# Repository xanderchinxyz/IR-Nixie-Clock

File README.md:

# IR-Nixie-Clock
All of the code and PCB files for my RGBW Neopixel Matrix

Check out the YouTube video: https://youtu.be/nEOyhyJHx2M

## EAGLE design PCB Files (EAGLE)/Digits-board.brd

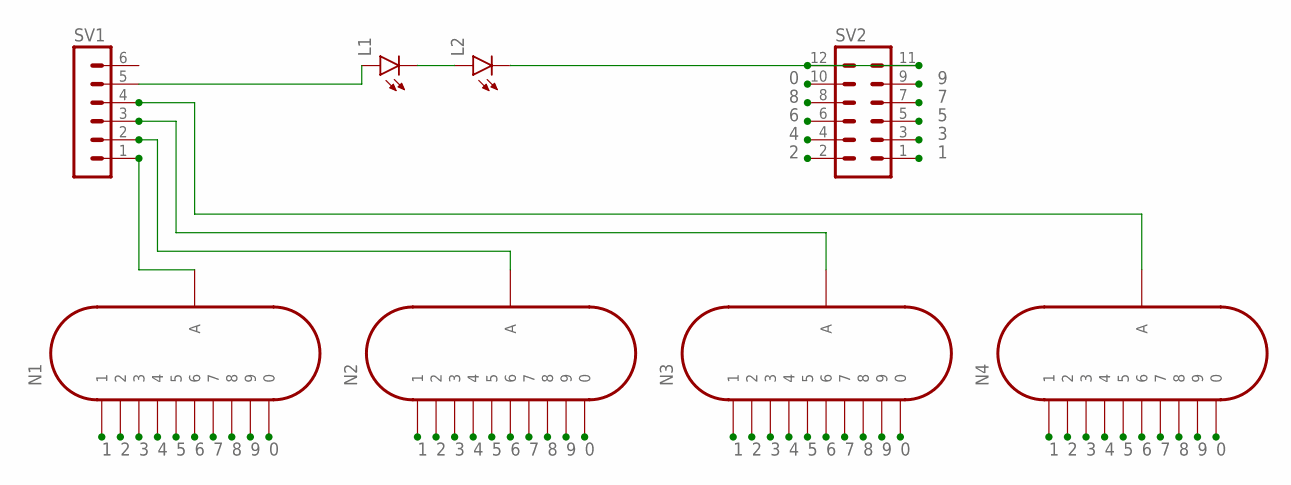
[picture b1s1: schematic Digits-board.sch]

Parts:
L1, L2: LED5MM
N1, N2, N3, N4: IN-12A; IN-12
SV1: MA06-1
SV2: MA06-2

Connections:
0: N1.0, N2.0, N3.0, N4.0, SV2.10
1: N1.1, N2.1, N3.1, N4.1, SV2.1
2: N1.2, N2.2, N3.2, N4.2, SV2.2
3: N1.3, N2.3, N3.3, N4.3, SV2.3
4: N1.4, N2.4, N3.4, N4.4, SV2.4
5: N1.5, N2.5, N3.5, N4.5, SV2.5
6: N1.6, N2.6, N3.6, N4.6, SV2.6
7: N1.7, N2.7, N3.7, N4.7, SV2.7
8: N1.8, N2.8, N3.8, N4.8, SV2.8
9: N1.9, N2.9, N3.9, N4.9, SV2.9
unnamed: L1.K (C), L2.A
unnamed: L1.A, SV1.5
unnamed: N4.A, SV1.4
unnamed: N3.A, SV1.3
unnamed: N2.A, SV1.2
unnamed: N1.A, SV1.1
unnamed: L2.K (C), SV2.11, SV2.12

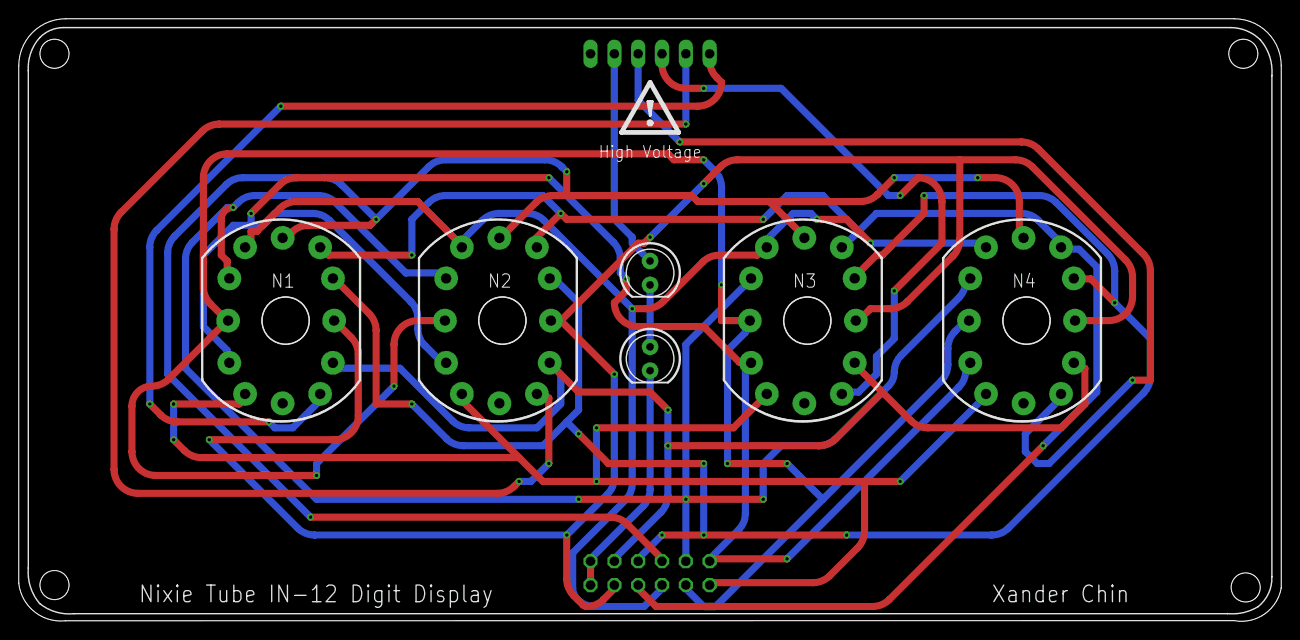
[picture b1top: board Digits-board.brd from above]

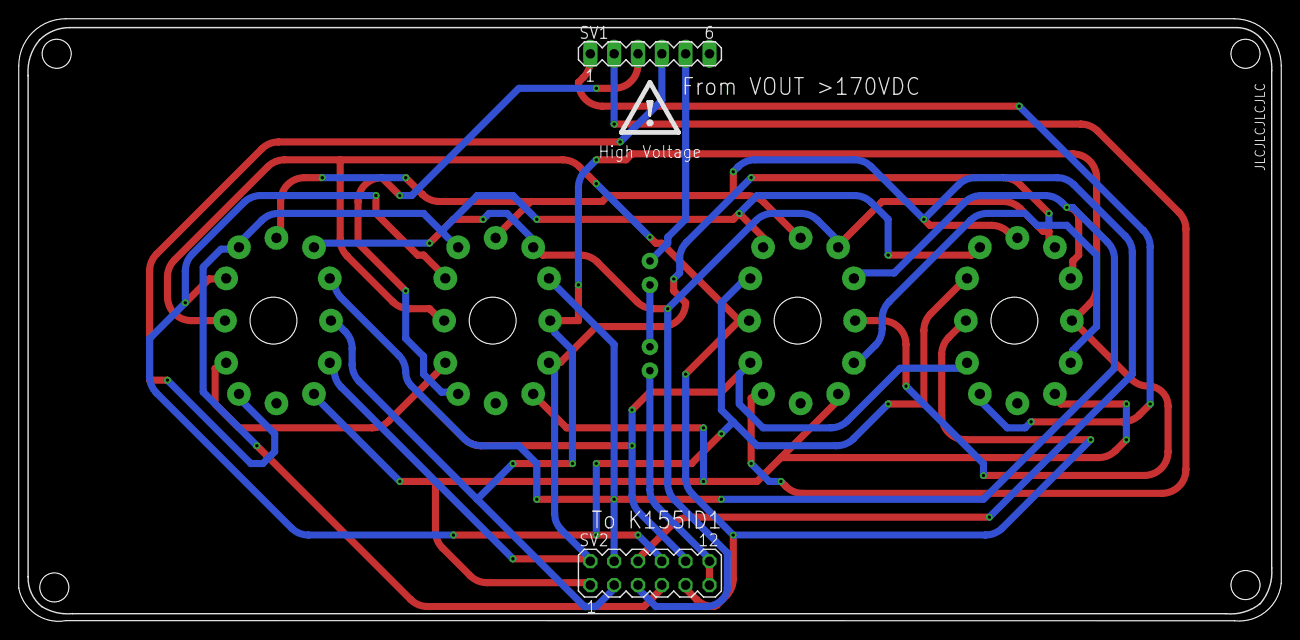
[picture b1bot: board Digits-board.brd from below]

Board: 2 copper layers, 134.6 x 64.2 mm, 10 parts (3 on the bottom side), 17 nets.

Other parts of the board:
U$1, U$2: CAUTION-HIGH-VOLTAGE

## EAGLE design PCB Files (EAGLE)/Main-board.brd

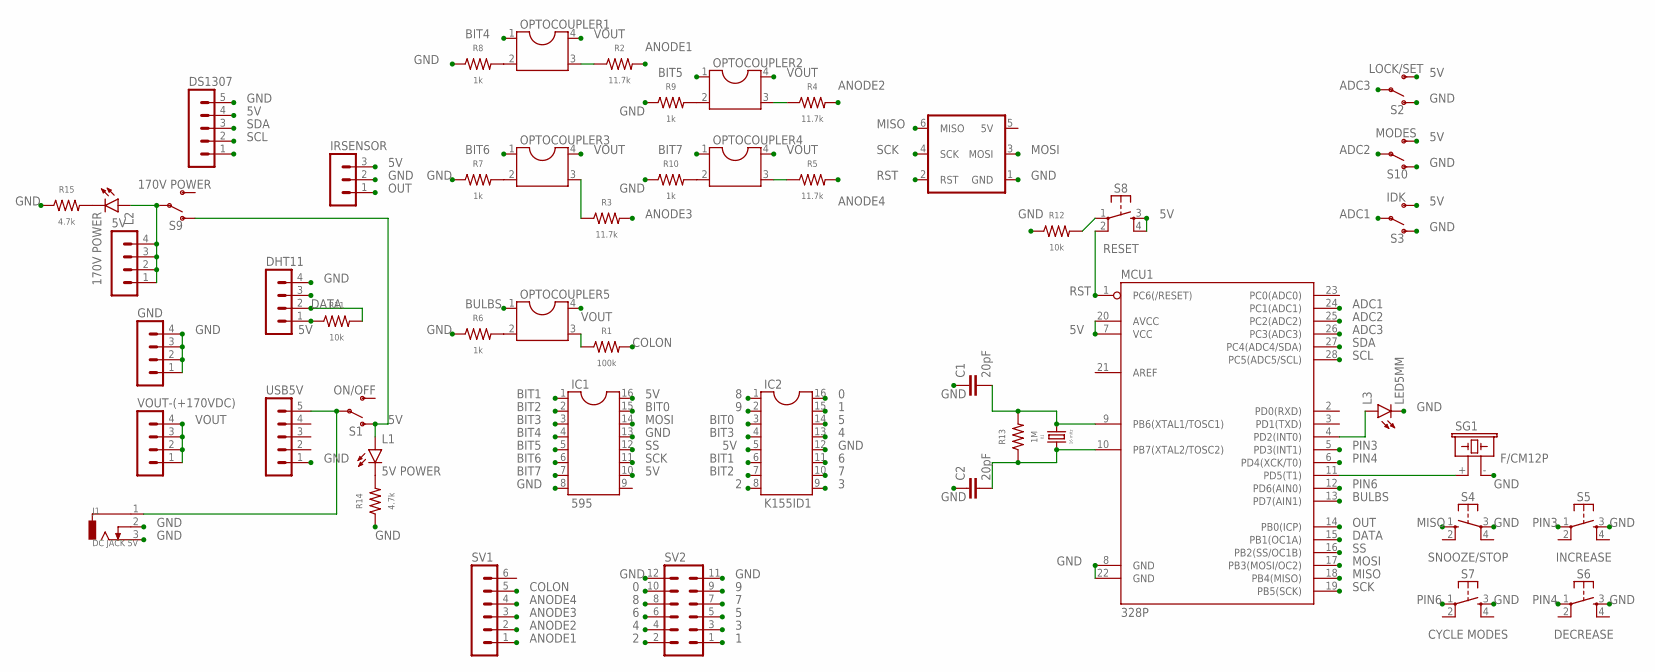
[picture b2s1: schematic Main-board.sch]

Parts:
5V: MA04-1
C1, C2: 20pF; CAP-PTH-2.54
DHT11: MA04-1
DS1307: MA05-1
GND: MA04-1
H1: ISP_HEADER; ICSP
IC1: 595; DIL16
IC2: K155ID1; DIL16
IRSENSOR: MA03-1
J1: DC JACK 5V; PJ-202AH
L1: 5V POWER; LED3MM
L2: 170V POWER; LED3MM
L3: LED5MM
MCU1: 328P; DIP28
OPTOCOUPLER1, OPTOCOUPLER2, OPTOCOUPLER3, OPTOCOUPLER4, OPTOCOUPLER5: DIL4; DIL04
R1: 100k; 0207/10
R2, R3, R4, R5: 11.7k; 0207/10
R6, R7, R8, R9, R10: 1k; 0207/10
R11, R12: 10k; 0207/10
R13: 1M; 0207/10
R14, R15: 4.7k; 0207/10
S1: ON/OFF; EG1218
S2: LOCK/SET; EG1218
S3: IDK; EG1218
S4: SNOOZE/STOP; B3F-40XX-ROUND
S5: INCREASE; TACTILE_SWITCH_PTH_6.0MM
S6: DECREASE; TACTILE_SWITCH_PTH_6.0MM
S7: CYCLE MODES; TACTILE_SWITCH_PTH_6.0MM
S8: RESET; TACTILE_SWITCH_PTH_6.0MM
S9: 170V POWER; EG1218
S10: MODES; EG1218
SG1: F/CM12P
SV1: MA06-1
SV2: MA06-2
USB5V: MA05-1
VOUT-(+170VDC): MA04-1
X1: 16 mHz; HC49US

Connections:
0: IC2.16, SV2.10
1: IC2.15, SV2.1
2: IC2.8, SV2.2
3: IC2.9, SV2.3
4: IC2.13, SV2.4
5: IC2.14, SV2.5
5V: DHT11.1, DS1307.4, H1.5 (5V), IC1.10, IC1.16, IC2.5, IRSENSOR.3, L1.A, MCU1.7 (VCC), MCU1.20 (AVCC), R11.1, S1.O, S2.S, S3.S, S8.3 (S), S8.4 (S1), S9.O, S10.S
6: IC2.11, SV2.6
7: IC2.10, SV2.7
8: IC2.1, SV2.8
9: IC2.2, SV2.9
ADC1: MCU1.24 (PC1(ADC1)), S3.P
ADC2: MCU1.25 (PC2(ADC2)), S10.P
ADC3: MCU1.26 (PC3(ADC3)), S2.P
ANODE1: R2.2, SV1.1
ANODE2: R4.2, SV1.2
ANODE3: R3.2, SV1.3
ANODE4: R5.2, SV1.4
BIT0: IC1.15, IC2.3
BIT1: IC1.1, IC2.6
BIT2: IC1.2, IC2.7
BIT3: IC1.3, IC2.4
BIT4: IC1.4, OPTOCOUPLER1.1
BIT5: IC1.5, OPTOCOUPLER2.1
BIT6: IC1.6, OPTOCOUPLER3.1
BIT7: IC1.7, OPTOCOUPLER4.1
BULBS: MCU1.13 (PD7(AIN1)), OPTOCOUPLER5.1
COLON: R1.2, SV1.5
DATA: DHT11.2, MCU1.15 (PB1(OC1A)), R11.2
GND: C1.1, C2.1, DHT11.4, DS1307.5, GND.1, GND.2, GND.3, GND.4, H1.1 (GND), IC1.8, IC1.13, IC2.12, IRSENSOR.2, J1.2, J1.3, L3.K (C), MCU1.8 (GND), MCU1.22 (GND), R6.1, R7.1, R8.1, R9.1, R10.1, R12.1, R14.1, R15.1, S2.O, S3.O, S4.3, S5.3 (S), S6.3 (S), S7.3 (S), S10.O, SG1.- (2), SV2.11, SV2.12, USB5V.1
MISO: H1.6 (MISO), MCU1.18 (PB4(MISO)), S4.1 (S)
MOSI: H1.3 (MOSI), IC1.14, MCU1.17 (PB3(MOSI/OC2))
unnamed: OPTOCOUPLER3.3, R3.1
unnamed: L1.K (C), R14.2
unnamed: OPTOCOUPLER1.3, R2.1
unnamed: OPTOCOUPLER2.3, R4.1
unnamed: OPTOCOUPLER5.2, R6.2
unnamed: OPTOCOUPLER3.2, R7.2
unnamed: OPTOCOUPLER1.2, R8.2
unnamed: OPTOCOUPLER2.2, R9.2
unnamed: OPTOCOUPLER4.2, R10.2
unnamed: OPTOCOUPLER4.3, R5.1
unnamed: L2.K (C), R15.2
unnamed: R12.2, S8.1
unnamed: OPTOCOUPLER5.3, R1.1
unnamed: C1.2, MCU1.9 (PB6(XTAL1/TOSC1)), R13.2, X1.2
unnamed: C2.2, MCU1.10 (PB7(XTAL2/TOSC2)), R13.1, X1.1
unnamed: 5V.1, 5V.2, 5V.3, 5V.4, L2.A, S9.P
unnamed: J1.1, S1.P, USB5V.5
unnamed: L3.A, MCU1.4 (PD2(INT0))
unnamed: MCU1.11 (PD5(T1)), SG1.+ (1)
OUT: IRSENSOR.1, MCU1.14 (PB0(ICP))
PIN3: MCU1.5 (PD3(INT1)), S5.1
PIN4: MCU1.6 (PD4(XCK/T0)), S6.1
PIN6: MCU1.12 (PD6(AIN0)), S7.1
RST: H1.2 (RST), MCU1.1 (PC6(/RESET)), S8.2 (P1)
SCK: H1.4 (SCK), IC1.11, MCU1.19 (PB5(SCK))
SCL: DS1307.2, MCU1.28 (PC5(ADC5/SCL))
SDA: DS1307.3, MCU1.27 (PC4(ADC4/SDA))
SS: IC1.12, MCU1.16 (PB2(SS/OC1B))
VOUT: OPTOCOUPLER1.4, OPTOCOUPLER2.4, OPTOCOUPLER3.4, OPTOCOUPLER4.4, OPTOCOUPLER5.4, VOUT-(+170VDC).1, VOUT-(+170VDC).2, VOUT-(+170VDC).3, VOUT-(+170VDC).4

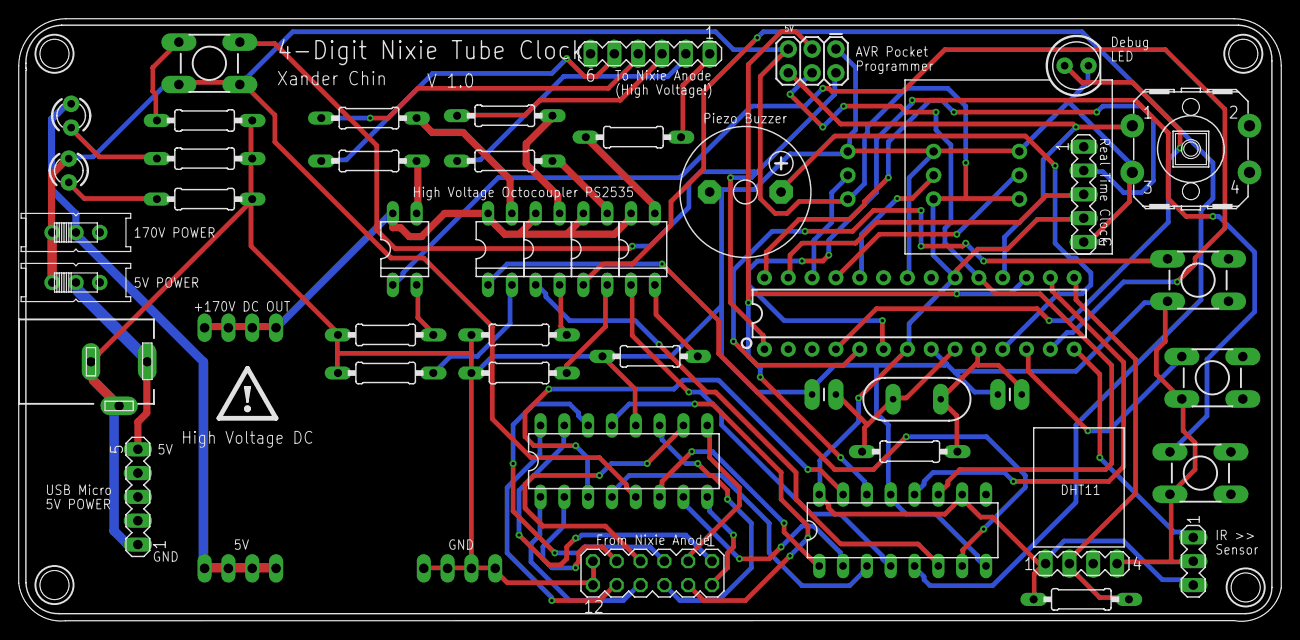
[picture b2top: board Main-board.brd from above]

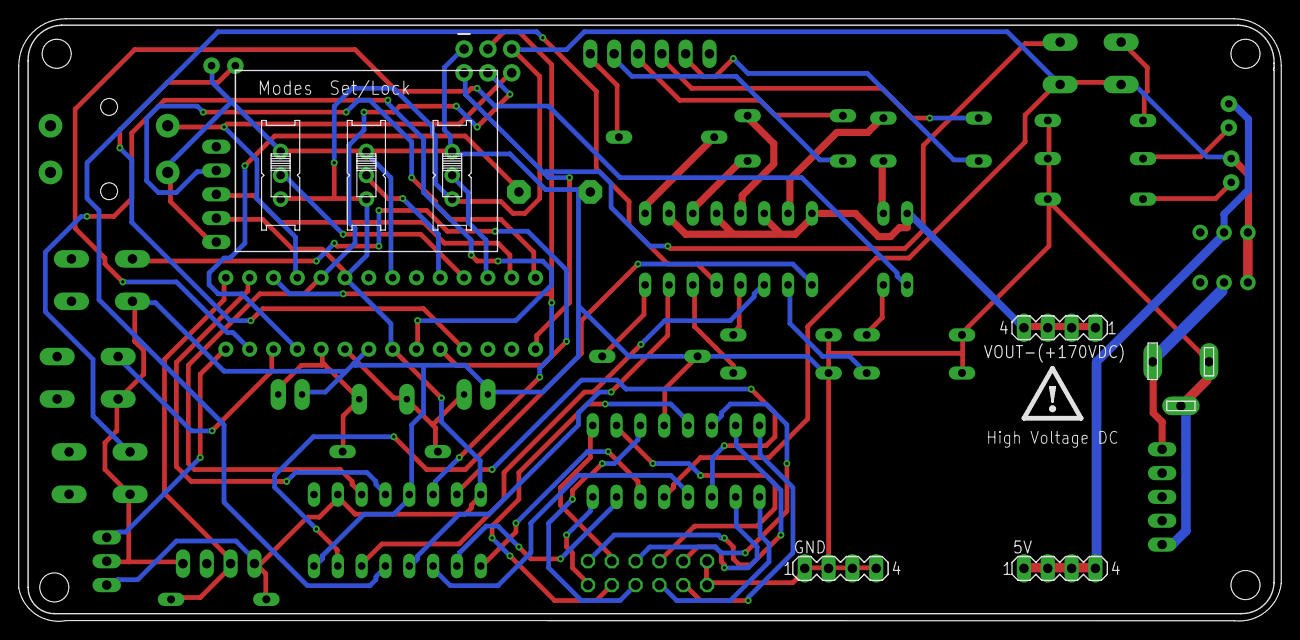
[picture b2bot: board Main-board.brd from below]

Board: 2 copper layers, 134.6 x 64.2 mm, 57 parts (7 on the bottom side), 61 nets.

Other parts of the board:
U$1, U$2, U$3, U$4: MOUNTINGHOLE_3.2MM_PLATEDTHIN
U$5, U$6: CAUTION-HIGH-VOLTAGE

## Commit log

2024-02-25 Uploaded all files
